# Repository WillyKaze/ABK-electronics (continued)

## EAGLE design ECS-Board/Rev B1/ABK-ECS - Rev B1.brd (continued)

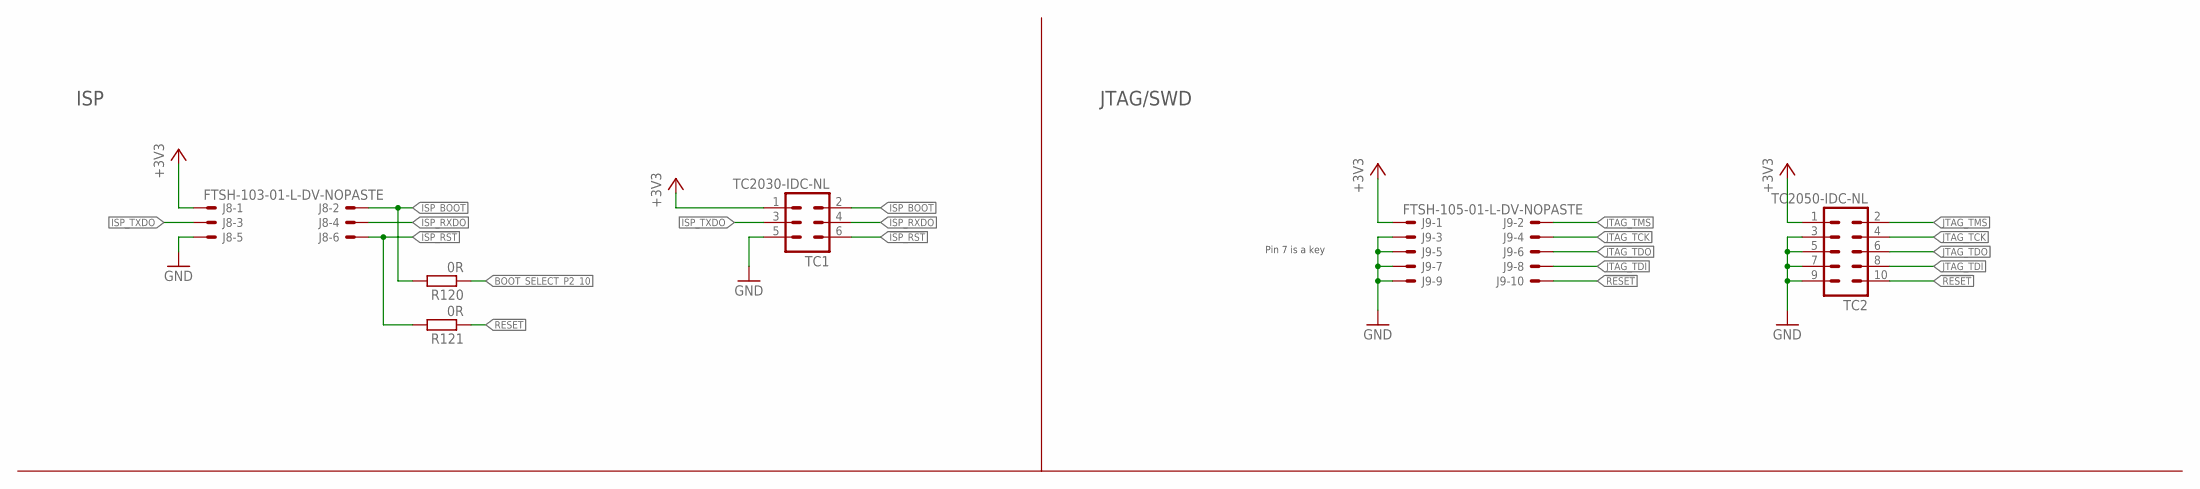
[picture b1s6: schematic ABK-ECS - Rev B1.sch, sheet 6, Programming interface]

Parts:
J8: FTSH-103-01-L-DV-NOPASTE
J9: FTSH-105-01-L-DV-NOPASTE
R120, R121: 0R; R0603; MPN MCMR06X000 PTL
TC1: TC2030-IDC-NL
TC2: TC2050-IDC-NL

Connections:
!ISP_BOOT: J8.2, R120.2, TC1.2
!ISP_RST: J8.6, R121.2, TC1.6
!RESET: J9.10, R121.1, TC2.10; also elsewhere on the board
+3V3: J8.1, J9.1, TC1.1, TC2.1; also elsewhere on the board
BOOT_SELECT_P2_10: R120.1; also elsewhere on the board
GND: J8.5, J9.3, J9.5, J9.7, J9.9, TC1.5, TC2.3, TC2.5, TC2.7, TC2.9; also elsewhere on the board
ISP_RXDO: J8.4, TC1.4; also elsewhere on the board
ISP_TXDO: J8.3, TC1.3; also elsewhere on the board
JTAG_TCK: J9.4, TC2.4; also elsewhere on the board
JTAG_TDI: J9.8, TC2.8; also elsewhere on the board
JTAG_TDO: J9.6, TC2.6; also elsewhere on the board
JTAG_TMS: J9.2, TC2.2; also elsewhere on the board

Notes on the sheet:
JTAG/SWD
Pin 7 is a key
ISP

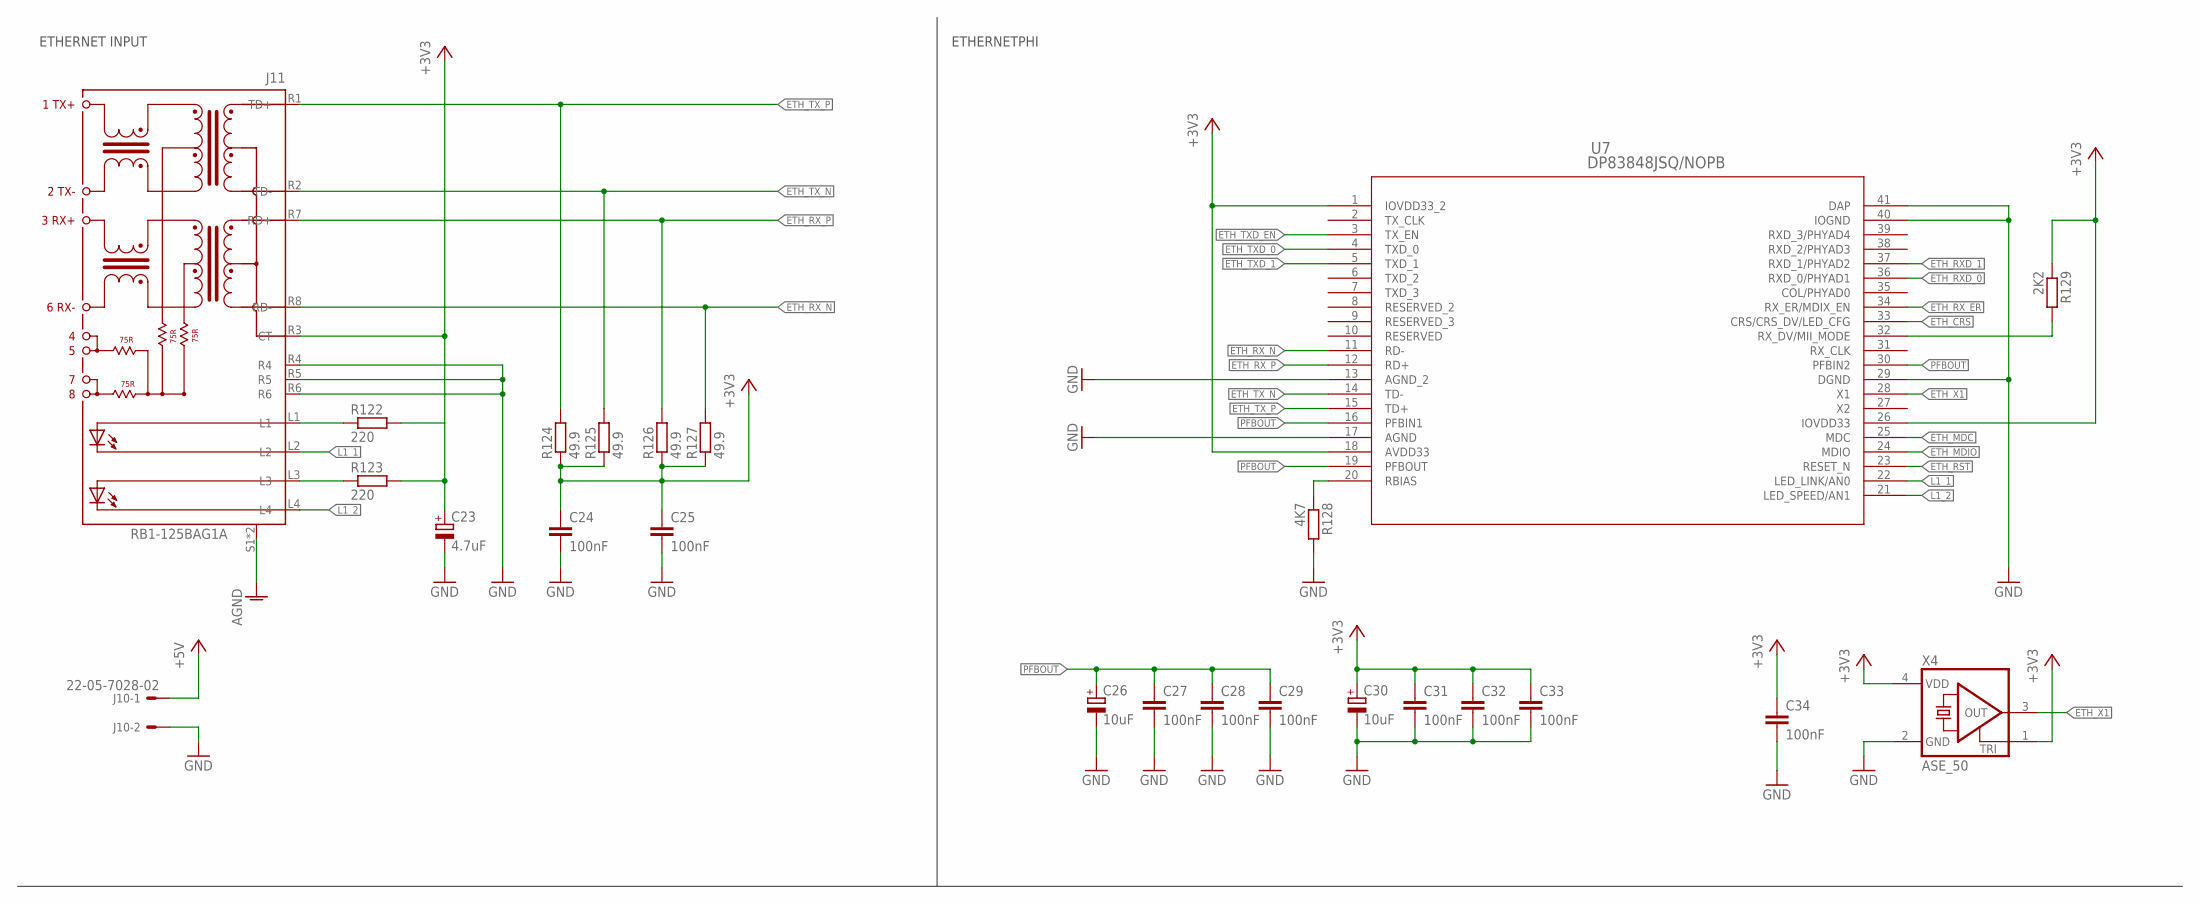
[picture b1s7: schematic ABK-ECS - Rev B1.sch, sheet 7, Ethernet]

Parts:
C23: 4.7uF; CT3216; MPN F931A475MAA
C24, C25, C27, C28, C29, C31, C32, C33, C34: 100nF; C0603; MPN MC0603B104K250CT
C26, C30: 10uF; CT3216; MPN F931A106MAA
J10: 22-05-7028-02; 7395-02; MPN 22-05-7028
J11: RB1-125BAG1A; WIZNET_RB1-125BAG1A
R122, R123: 220; R0603; MPN MCMR06X2200FTL
R124, R125, R126, R127: 49.9; R0603; MPN MCMR06X49R9FTL
R128: 4K7; R0603; MPN MCMR06X4701FTL
R129: 2K2; R0603; MPN MCMR06X2201FTL
U7: DP83848JSQ/NOPB; SQA40B; MPN DP83848JSQ/NOPB
X4: ASE_50; ASE; MPN ASE-50.000MHZ-LC-T

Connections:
+3V3: C23.+, C24.1, C25.1, C30.+, C31.1, C32.1, C33.1, C34.1, J11.R3 (CT), R122.2, R123.2, R124.1, R125.1, R126.1, R127.1, R129.1, U7.1 (IOVDD33_2), U7.18 (AVDD33), U7.26 (IOVDD33), X4.1 (TRI), X4.4 (VDD); also elsewhere on the board
+5V: J10.1; also elsewhere on the board
AGND: J11.S1, J11.S2
ETH_CRS: U7.33 (CRS/CRS_DV/LED_CFG); also elsewhere on the board
ETH_MDC: U7.25 (MDC); also elsewhere on the board
ETH_MDIO: U7.24 (MDIO); also elsewhere on the board
ETH_RST: U7.23 (RESET_N)
ETH_RXD_0: U7.36 (RXD_0/PHYAD1); also elsewhere on the board
ETH_RXD_1: U7.37 (RXD_1/PHYAD2); also elsewhere on the board
ETH_RX_ER: U7.34 (RX_ER/MDIX_EN); also elsewhere on the board
ETH_RX_N: J11.R8 (RD-), R127.2, U7.11 (RD-)
ETH_RX_P: J11.R7 (RD+), R126.2, U7.12 (RD+)
ETH_TXD_0: U7.4 (TXD_0); also elsewhere on the board
ETH_TXD_1: U7.5 (TXD_1); also elsewhere on the board
ETH_TXD_EN: U7.3 (TX_EN); also elsewhere on the board
ETH_TX_N: J11.R2 (TD-), R125.2, U7.14 (TD-)
ETH_TX_P: J11.R1 (TD+), R124.2, U7.15 (TD+)
ETH_X1: U7.28 (X1), X4.3 (OUT); also elsewhere on the board
GND: C23.-, C24.2, C25.2, C26.-, C27.2, C28.2, C29.2, C30.-, C31.2, C32.2, C33.2, C34.2, J10.2, J11.R4, J11.R5, J11.R6, R128.2, U7.13 (AGND_2), U7.17 (AGND), U7.29 (DGND), U7.40 (IOGND), U7.41 (DAP), X4.2 (GND); also elsewhere on the board
L1_1: J11.L2, U7.22 (LED_LINK/AN0)
L1_2: J11.L4, U7.21 (LED_SPEED/AN1)
MII_MODE: R129.2, U7.32 (RX_DV/MII_MODE)
unnamed: J11.L1, R122.1
unnamed: J11.L3, R123.1
unnamed: R128.1, U7.20 (RBIAS)
PFBOUT: C26.+, C27.1, C28.1, C29.1, U7.16 (PFBIN1), U7.19 (PFBOUT), U7.30 (PFBIN2)

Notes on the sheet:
ETHERNET INPUT
ETHERNETPHI

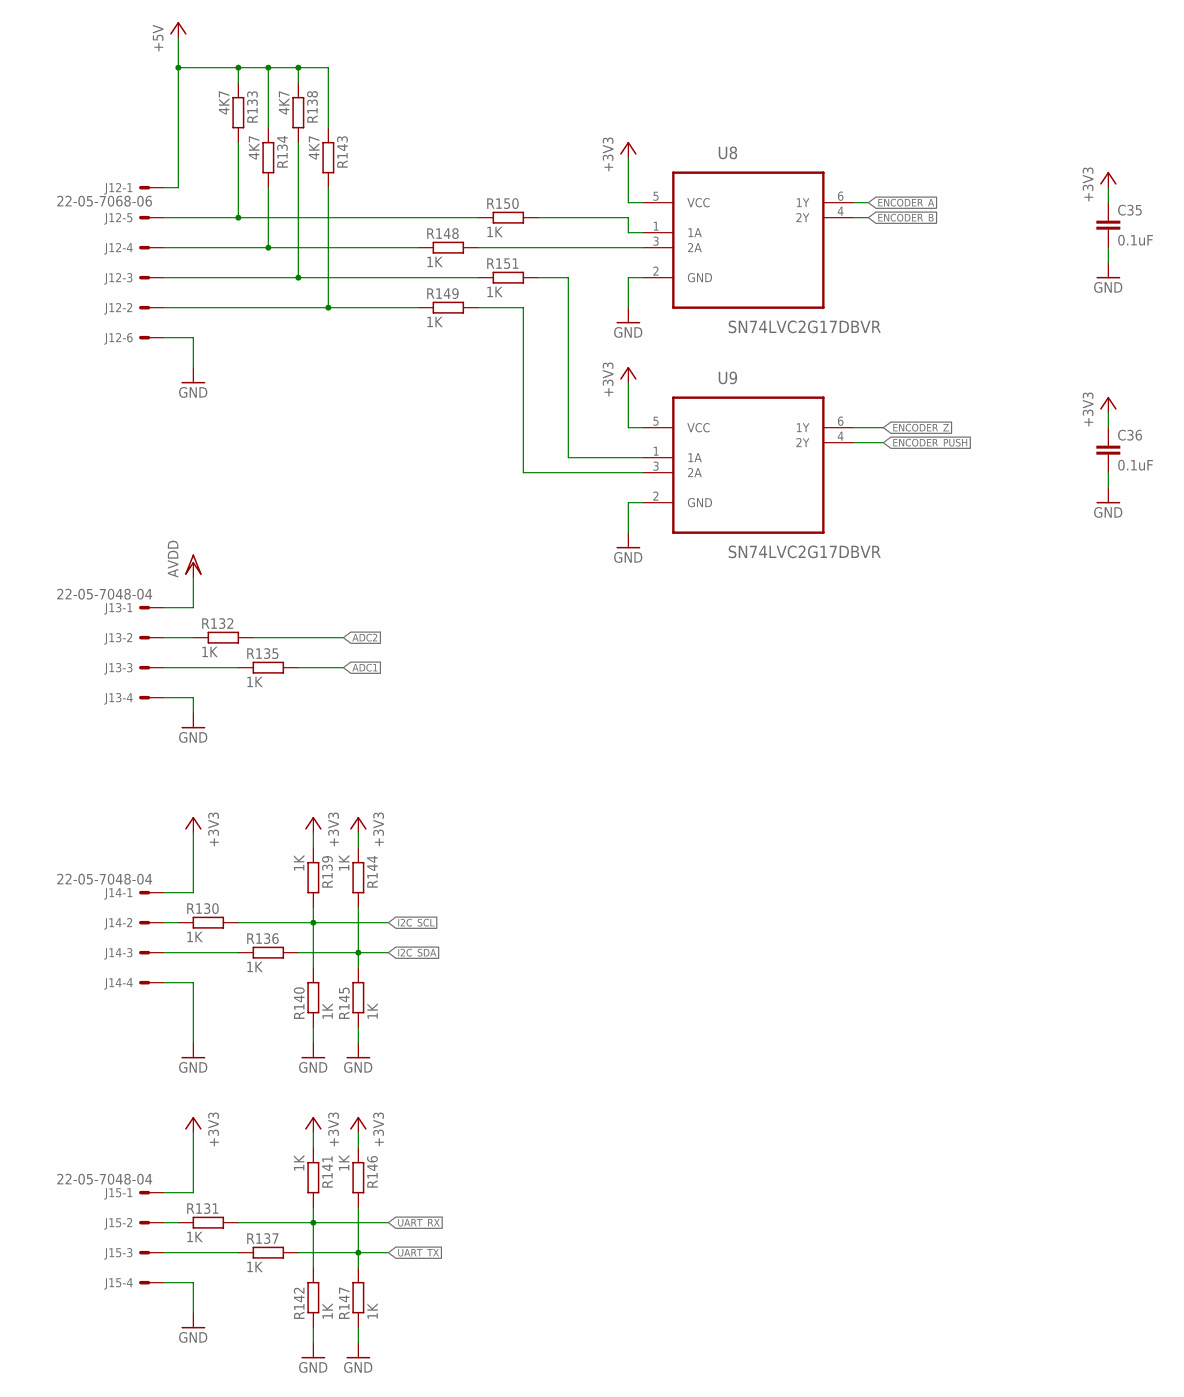
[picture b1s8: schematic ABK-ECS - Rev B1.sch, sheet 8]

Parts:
C35, C36: 0.1uF; C0603; MPN MC0603B104K160CT
J12: 22-05-7068-06; 7395-06; MPN 22-05-7058
J13, J14, J15: 22-05-7048-04; 7395-04
R130, R131, R132, R135, R136, R137, R139, R140, R141, R142, R144, R145, R146, R147, R148, R149, R150, R151: 1K; R0603; MPN MCMR06X1001FTL
R133, R134, R138, R143: 4K7; R0603; MPN MCMR06X2701FTL
U8, U9: SN74LVC2G17DBVR; SOT95P280X145-6N

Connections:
+3V3: C35.1, C36.1, J14.1, J15.1, R139.1, R141.1, R144.1, R146.1, U8.5 (VCC), U9.5 (VCC); also elsewhere on the board
+5V: J12.1, R133.1, R134.1, R138.1, R143.1; also elsewhere on the board
ADC1: R135.2; also elsewhere on the board
ADC2: R132.2; also elsewhere on the board
AVDD: J13.1; also elsewhere on the board
ENCODER_A: U8.6 (1Y); also elsewhere on the board
ENCODER_B: U8.4 (2Y); also elsewhere on the board
ENCODER_PUSH: U9.4 (2Y); also elsewhere on the board
ENCODER_Z: U9.6 (1Y); also elsewhere on the board
GND: C35.2, C36.2, J12.6, J13.4, J14.4, J15.4, R140.1, R142.1, R145.1, R147.1, U8.2 (GND), U9.2 (GND); also elsewhere on the board
I2C_SCL: R130.2, R139.2, R140.2; also elsewhere on the board
I2C_SDA: R136.2, R144.2, R145.2; also elsewhere on the board
unnamed: J12.5, R133.2, R150.1
unnamed: J12.4, R134.2, R148.1
unnamed: J12.3, R138.2, R151.1
unnamed: R149.2, U9.3 (2A)
unnamed: R148.2, U8.3 (2A)
unnamed: R150.2, U8.1 (1A)
unnamed: R151.2, U9.1 (1A)
unnamed: J12.2, R143.2, R149.1
unnamed: J13.2, R132.1
unnamed: J13.3, R135.1
unnamed: J14.2, R130.1
unnamed: J14.3, R136.1
unnamed: J15.2, R131.1
unnamed: J15.3, R137.1
UART_RX: R131.2, R141.2, R142.2; also elsewhere on the board
UART_TX: R137.2, R146.2, R147.2; also elsewhere on the board

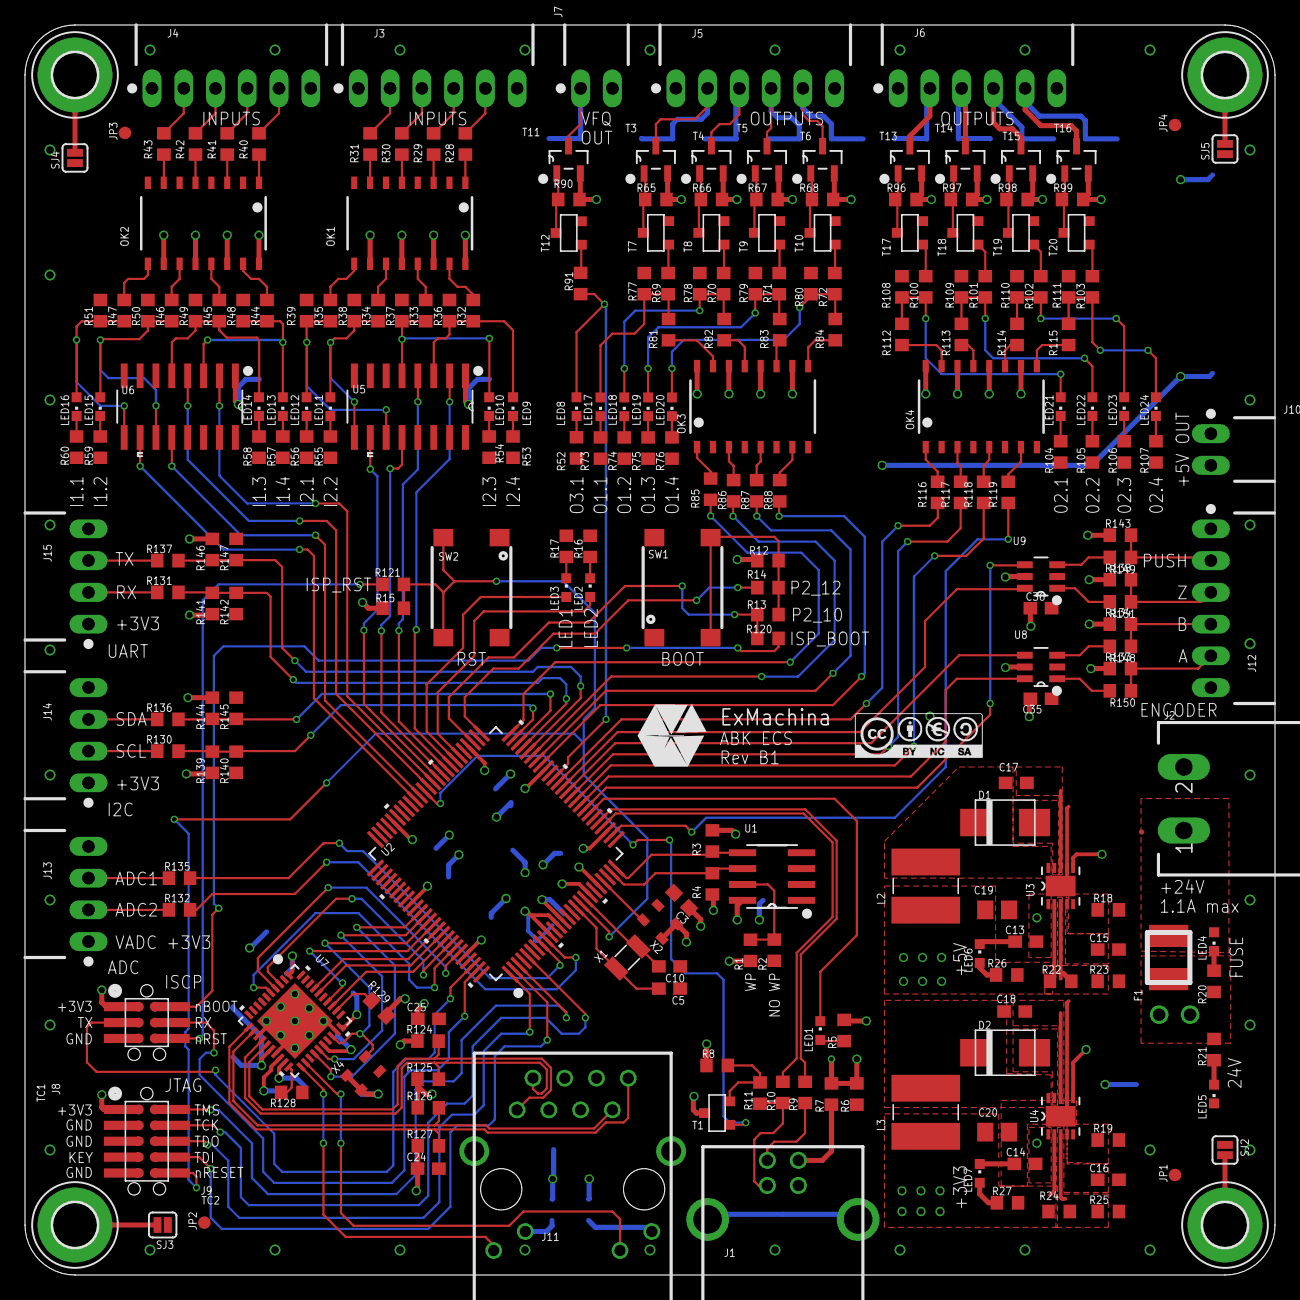
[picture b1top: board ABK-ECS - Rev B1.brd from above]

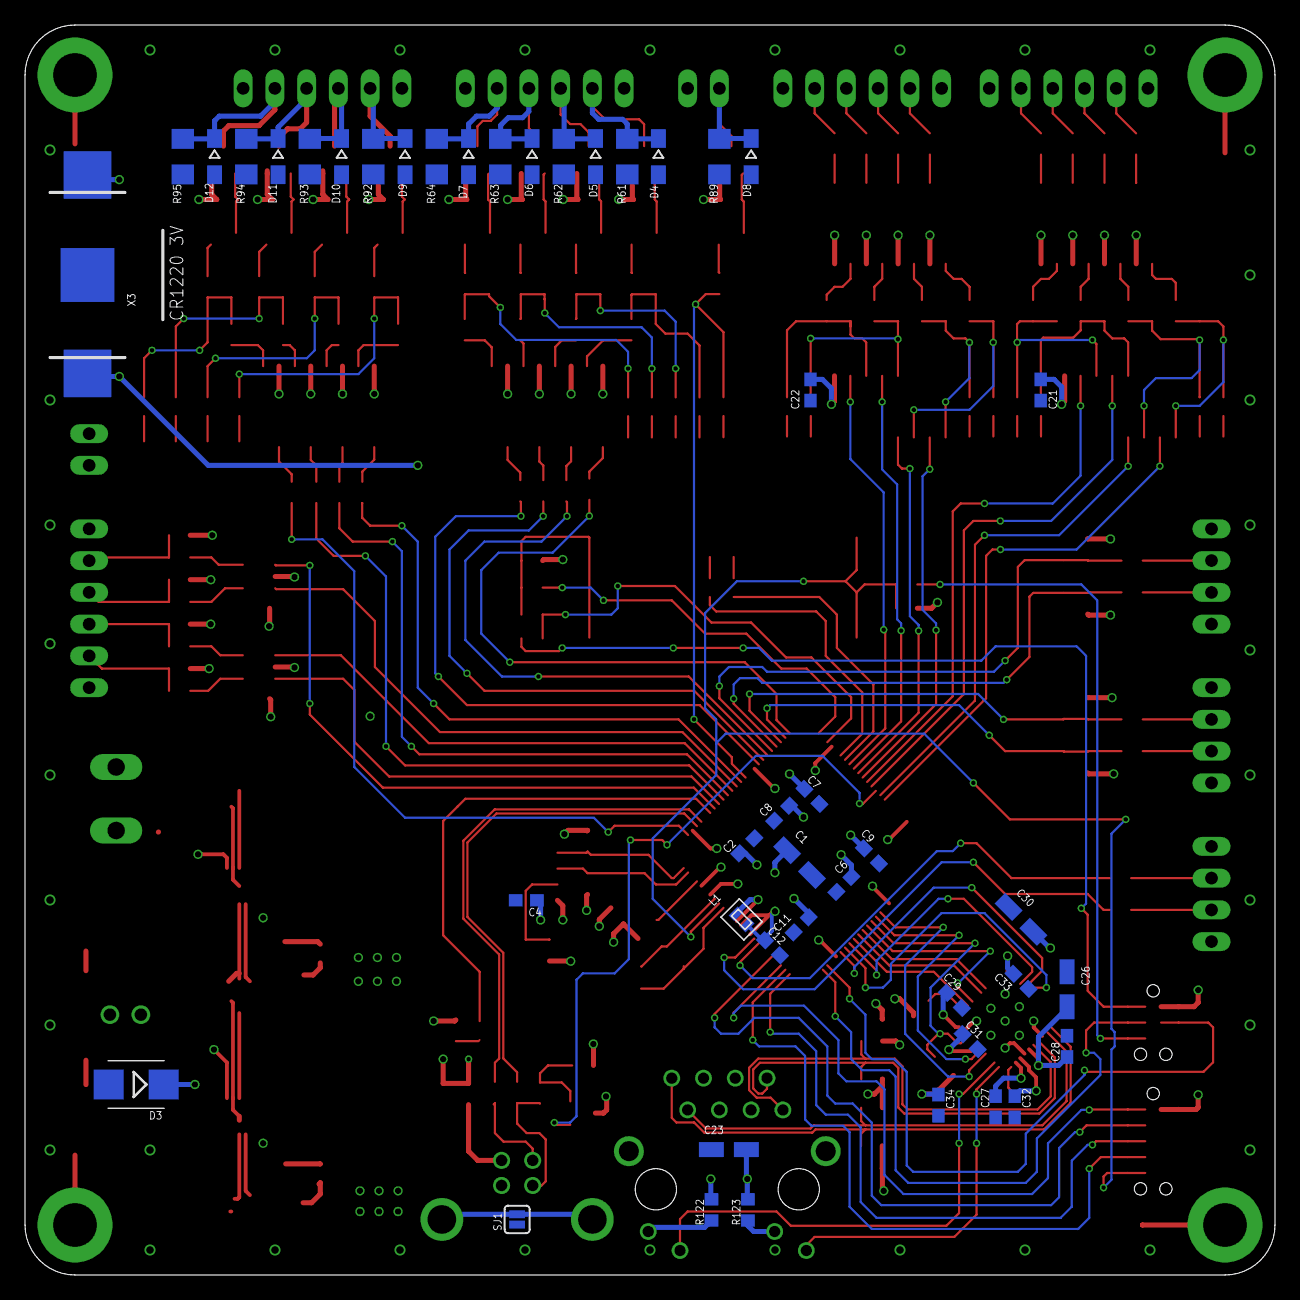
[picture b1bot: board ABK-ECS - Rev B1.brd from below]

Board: 4 copper layers, 100.0 x 100.0 mm, 297 parts (45 on the bottom side), 223 nets.

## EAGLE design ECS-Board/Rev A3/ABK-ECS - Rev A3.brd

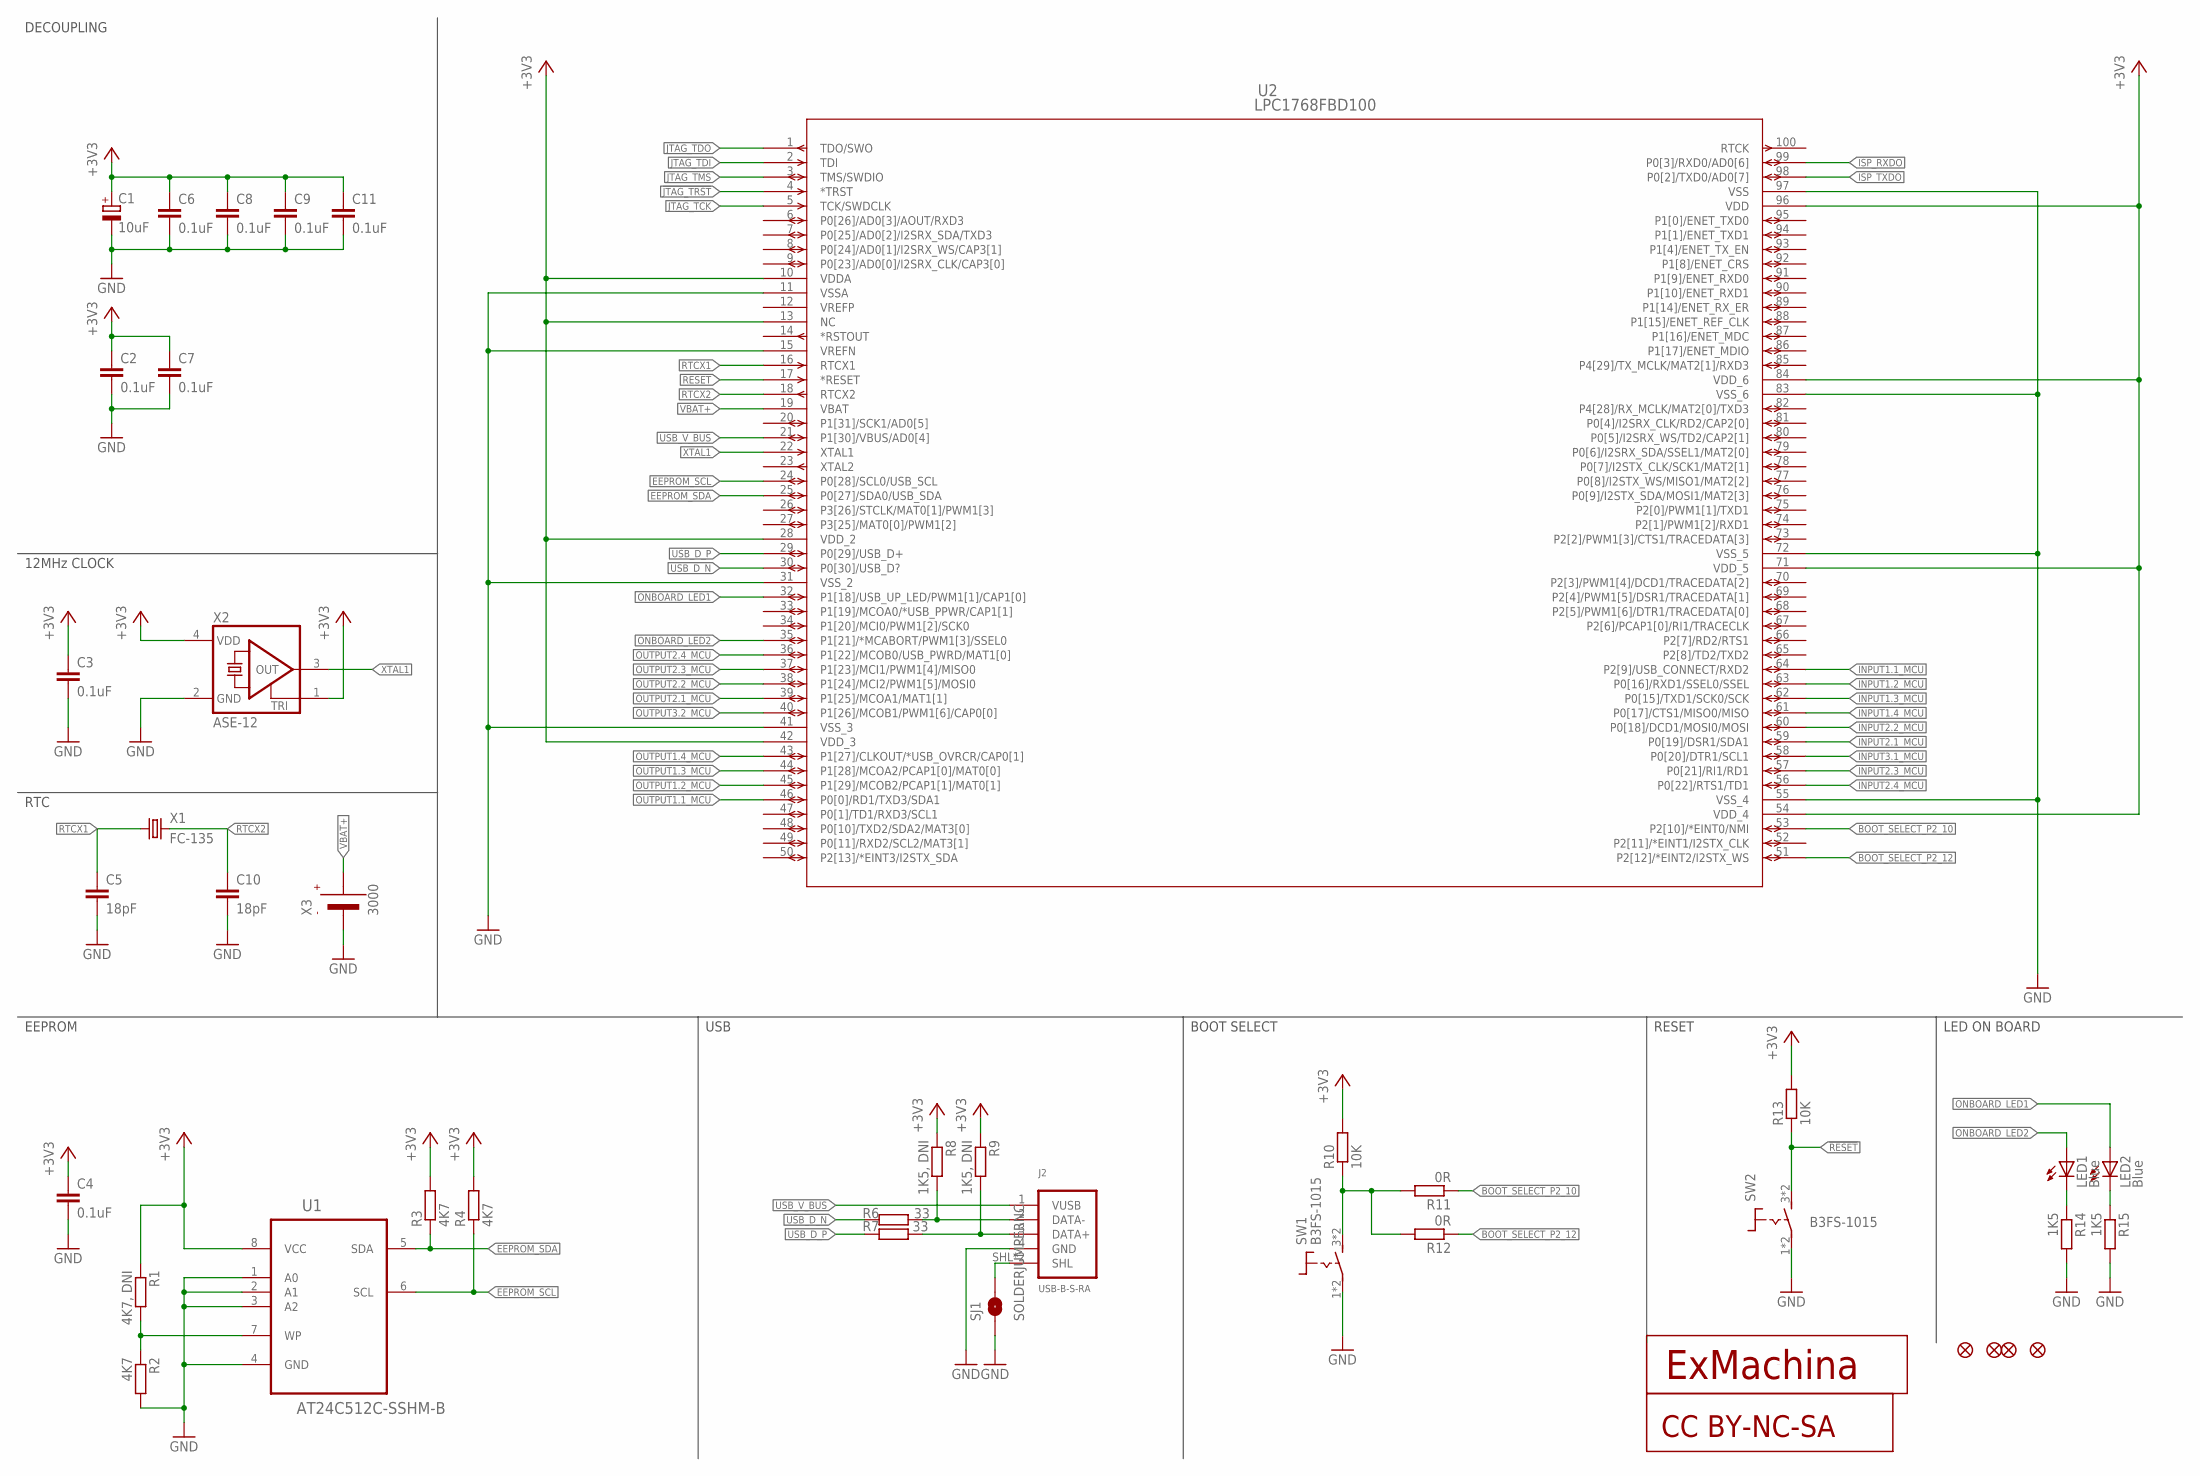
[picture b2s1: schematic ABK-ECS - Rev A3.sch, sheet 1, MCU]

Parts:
C1: 10uF; CT3216; MPN F931A106MAA
C2, C3, C4, C6, C7, C8, C9, C11: 0.1uF; C0603; MPN MC0603B104K160CT
C5, C10: 18pF; C0603; MPN GRM1885C1H180JA01D
CC1: CC-BY-NC-SA
J2: USB-B-S-RA; MPN USB-B-S-RA
JP1, JP2, JP3, JP4: FIDUCIAL1X2; FIDUCIAL-1X2
LED1, LED2: Blue; CHIPLED_0603; MPN OVS-0603
R1: 4K7, DNI; R0603; MPN RC0603FR-074K7L
R2, R3, R4: 4K7; R0603; MPN RC0603FR-074K7L
R6, R7: 33; R0603; MPN RC0603FR-0733RL
R8, R9: 1K5, DNI; R0603; MPN RC0603FR-071K5L
R10, R13: 10K; R0603; MPN RC0603FR-0710KL
R11, R12: 0R; R0603; MPN RC0603FR-070RL
R14, R15: 1K5; R0603; MPN RC0603FR-071K5L
SJ1: SOLDERJUMPERNC; SJ_2S
SW1, SW2: B3FS-1015; B3FS; MPN B3FS-1010
T1: EXMACHINA-LOGO-NAME; EXM-LOGO-BASELINE
U1: AT24C512C-SSHM-B; SOIC127P600X175-8N; MPN AT24C512C-SSHM-B
U2: LPC1768FBD100; SOT407-1; MPN LPC1768FBD100
X1: FC-135; MPN Q13FC13500004
X2: ASE-12; ASE; MPN ASE-12.000MHZ-LC-T
X3: 3000; MPN 3000

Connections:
!JTAG_TRST: U2.4 (*TRST)
!RESET: R13.1, SW2.3 (1), SW2.4 (1), U2.17 (*RESET); also elsewhere on the board
+3V3: C1.+, C2.1, C3.1, C4.1, C6.1, C7.1, C8.1, C9.1, C11.1, R1.1, R3.2, R4.2, R8.1, R9.1, R10.2, R13.2, U1.8 (VCC), U2.10 (VDDA), U2.13 (NC), U2.28 (VDD_2), U2.42 (VDD_3), U2.54 (VDD_4), U2.71 (VDD_5), U2.84 (VDD_6), U2.96 (VDD), X2.1 (TRI), X2.4 (VDD); also elsewhere on the board
BOOT_SELECT_P2_10: R11.1, U2.53 (P2[10]/*EINT0/NMI); also elsewhere on the board
BOOT_SELECT_P2_12: R12.1, U2.51 (P2[12]/*EINT2/I2STX_WS)
EEPROM_SCL: R4.1, U1.6 (SCL), U2.24 (P0[28]/SCL0/USB_SCL)
EEPROM_SDA: R3.1, U1.5 (SDA), U2.25 (P0[27]/SDA0/USB_SDA)
GND: C1.-, C2.2, C3.2, C4.2, C5.2, C6.2, C7.2, C8.2, C9.2, C10.2, C11.2, J2.4 (GND), R2.2, R14.2, R15.2, SJ1.1, SW1.1 (2), SW1.2, SW2.1 (2), SW2.2, U1.1 (A0), U1.2 (A1), U1.3 (A2), U1.4 (GND), U2.11 (VSSA), U2.15 (VREFN), U2.31 (VSS_2), U2.41 (VSS_3), U2.55 (VSS_4), U2.72 (VSS_5), U2.83 (VSS_6), U2.97 (VSS), X2.2 (GND), X3.- (VBAT-); also elsewhere on the board
INPUT1.1_MCU: U2.64 (P2[9]/USB_CONNECT/RXD2); also elsewhere on the board
INPUT1.2_MCU: U2.63 (P0[16]/RXD1/SSEL0/SSEL); also elsewhere on the board
INPUT1.3_MCU: U2.62 (P0[15]/TXD1/SCK0/SCK); also elsewhere on the board
INPUT1.4_MCU: U2.61 (P0[17]/CTS1/MISO0/MISO); also elsewhere on the board
INPUT2.1_MCU: U2.59 (P0[19]/DSR1/SDA1); also elsewhere on the board
INPUT2.2_MCU: U2.60 (P0[18]/DCD1/MOSI0/MOSI); also elsewhere on the board
INPUT2.3_MCU: U2.57 (P0[21]/RI1/RD1); also elsewhere on the board
INPUT2.4_MCU: U2.56 (P0[22]/RTS1/TD1); also elsewhere on the board
INPUT3.1_MCU: U2.58 (P0[20]/DTR1/SCL1); also elsewhere on the board
ISP_RXDO: U2.99 (P0[3]/RXD0/AD0[6]); also elsewhere on the board
ISP_TXDO: U2.98 (P0[2]/TXD0/AD0[7]); also elsewhere on the board
JTAG_TCK: U2.5 (TCK/SWDCLK); also elsewhere on the board
JTAG_TDI: U2.2 (TDI); also elsewhere on the board
JTAG_TDO: U2.1 (TDO/SWO); also elsewhere on the board
JTAG_TMS: U2.3 (TMS/SWDIO); also elsewhere on the board
unnamed: J2.3 (DATA+), R7.1, R9.2
unnamed: J2.2 (DATA-), R6.1, R8.2
unnamed: LED2.C, R15.1
unnamed: R10.1, R11.2, R12.2, SW1.3 (1), SW1.4 (1)
unnamed: R1.2, R2.1, U1.7 (WP)
unnamed: LED1.C, R14.1
unnamed: J2.SHL, J2.SHL1 (SHL), SJ1.2
ONBOARD_LED1: LED2.A, U2.32 (P1[18]/USB_UP_LED/PWM1[1]/CAP1[0])
ONBOARD_LED2: LED1.A, U2.35 (P1[21]/*MCABORT/PWM1[3]/SSEL0)
OUTPUT1.1_MCU: U2.46 (P0[0]/RD1/TXD3/SDA1); also elsewhere on the board
OUTPUT1.2_MCU: U2.45 (P1[29]/MCOB2/PCAP1[1]/MAT0[1]); also elsewhere on the board
OUTPUT1.3_MCU: U2.44 (P1[28]/MCOA2/PCAP1[0]/MAT0[0]); also elsewhere on the board
OUTPUT1.4_MCU: U2.43 (P1[27]/CLKOUT/*USB_OVRCR/CAP0[1]); also elsewhere on the board
OUTPUT2.1_MCU: U2.39 (P1[25]/MCOA1/MAT1[1]); also elsewhere on the board
OUTPUT2.2_MCU: U2.38 (P1[24]/MCI2/PWM1[5]/MOSI0); also elsewhere on the board
OUTPUT2.3_MCU: U2.37 (P1[23]/MCI1/PWM1[4]/MISO0); also elsewhere on the board
OUTPUT2.4_MCU: U2.36 (P1[22]/MCOB0/USB_PWRD/MAT1[0]); also elsewhere on the board
OUTPUT3.2_MCU: U2.40 (P1[26]/MCOB1/PWM1[6]/CAP0[0]); also elsewhere on the board
RTCX1: C5.1, U2.16 (RTCX1), X1.1
RTCX2: C10.1, U2.18 (RTCX2), X1.2
USB_D_N: R6.2, U2.30 (P0[30]/USB_D?)
USB_D_P: R7.2, U2.29 (P0[29]/USB_D+)
USB_V_BUS: J2.1 (VUSB), U2.21 (P1[30]/VBUS/AD0[4])
VBAT+: U2.19 (VBAT), X3.+1 (VBAT+), X3.+2 (VBAT+)
VREFP: U2.12 (VREFP)
XTAL1: U2.22 (XTAL1), X2.3 (OUT)

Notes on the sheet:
USB
BOOT SELECT
LED ON BOARD
RESET
EEPROM
RTC
12MHz CLOCK
DECOUPLING

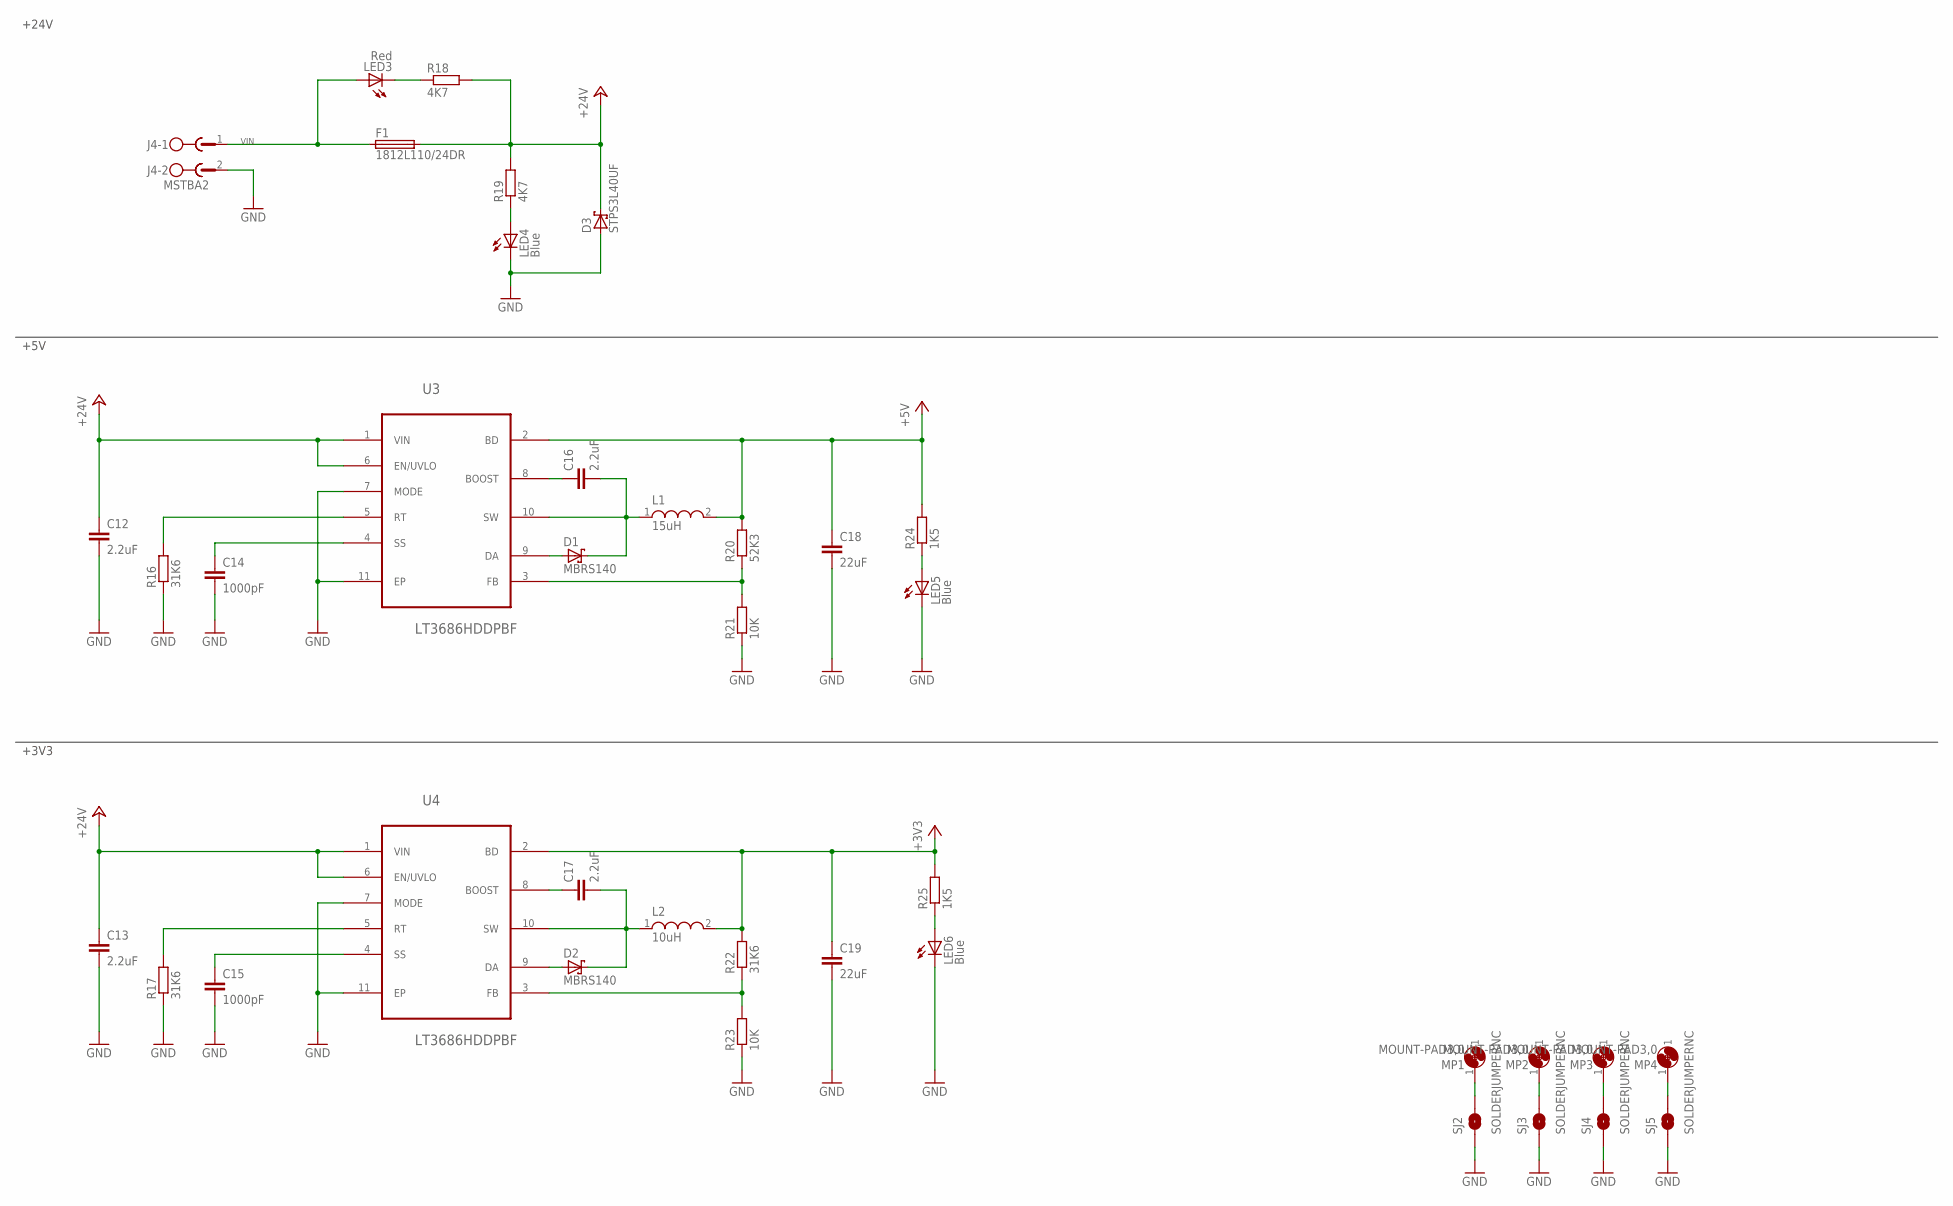
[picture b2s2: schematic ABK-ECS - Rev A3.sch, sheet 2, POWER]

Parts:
C12, C13, C16, C17: 2.2uF; C0603; MPN GRT188R61H225KE13D
C14, C15: 1000pF; C0603; MPN GRM188R71H102KA01D
C18, C19: 22uF; C0805; MPN C0805C226M9PACTU
D1, D2: MBRS140; DO-214AA; MPN MBRS140T3G
D3: STPS3L40UF; SMB
F1: 1812L110/24DR; LITTLEFUSE_SMD; MPN 3557
J4: MSTBA2
L1: 15uH; WE-PD2_5848/5820; MPN 744774115
L2: 10uH; WE-PD2_5848/5820; MPN 74477410
LED3: Red; CHIPLED_0603; MPN OVS-0608
LED4, LED5, LED6: Blue; CHIPLED_0603; MPN OVS-0603
MP1, MP2, MP3, MP4: MOUNT-PAD3,0; P3,0
R16, R17, R22: 31K6; R0603; MPN MCMR06X3162FTL
R18, R19: 4K7; R0603; MPN RC0603FR-074K7L
R20: 52K3; R0603; MPN MC0063W0603152K3
R21, R23: 10K; R0603; MPN RC0603FR-0710KL
R24, R25: 1K5; R0603; MPN RC0603FR-071K5L
SJ2, SJ3, SJ4, SJ5: SOLDERJUMPERNC; SJ_2S
U3, U4: LT3686HDDPBF; DFN300X300X80-11N

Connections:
1: MP1.1, SJ2.2
2: MP2.1, SJ3.2
3: MP3.1, SJ4.2
4: MP4.1, SJ5.2
+3V3: C19.1, L2.2, R22.2, R25.2, U4.2 (BD); also elsewhere on the board
+5V: C18.1, L1.2, R20.2, R24.2, U3.2 (BD); also elsewhere on the board
+24V: C12.1, C13.1, D3.C, F1.2, R18.2, R19.2, U3.1 (VIN), U3.6 (EN/UVLO), U4.1 (VIN), U4.6 (EN/UVLO); also elsewhere on the board
GND: C12.2, C13.2, C14.2, C15.2, C18.2, C19.2, D3.A, J4.2, LED4.C, LED5.C, LED6.C, R16.1, R17.1, R21.1, R23.1, SJ2.1, SJ3.1, SJ4.1, SJ5.1, U3.7 (MODE), U3.11 (EP), U4.7 (MODE), U4.11 (EP); also elsewhere on the board
unnamed: R16.2, U3.5 (RT)
unnamed: C14.1, U3.4 (SS)
unnamed: R17.2, U4.5 (RT)
unnamed: C15.1, U4.4 (SS)
unnamed: R20.1, R21.2, U3.3 (FB)
unnamed: C16.1, U3.8 (BOOST)
unnamed: C16.2, D1.C, L1.1, U3.10 (SW)
unnamed: D1.A, U3.9 (DA)
unnamed: R22.1, R23.2, U4.3 (FB)
unnamed: C17.1, U4.8 (BOOST)
unnamed: C17.2, D2.C, L2.1, U4.10 (SW)
unnamed: D2.A, U4.9 (DA)
unnamed: LED4.A, R19.1
unnamed: LED3.C, R18.1
unnamed: LED6.A, R25.1
unnamed: LED5.A, R24.1
VIN: F1.1, J4.1, LED3.A

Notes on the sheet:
+5V
+3V3
+24V
